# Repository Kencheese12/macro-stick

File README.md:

# macro-stick

縦型Bluetoothマクロパッドの設計データ一式。CKW12ホイールエンコーダ×1＋MXスイッチ×4の1列レイアウト、MCUは Seeed XIAO nRF52840 をエンコーダの下（基板裏面）に配置するB案。全長111.7mm。

## 中身

- `kicad/` — KiCad 10 基板データ
  - `mpad_b.kicad_pcb` — B案の基板（配線済み：Freerouting自動配線＋手修正、DRCクリーン）
  - `mpad_a.kicad_pcb` — A案（参考）
  - `lib/` — 自作フットプリント（mpad.pretty）とSeeed XIAOフットプリント
  - `gen_mpad_b.py` / `gen_mpad.py` — 基板生成スクリプト（KiCad同梱Pythonで実行）
- `case/mpad_case.scad` — 筐体・底板・プレート・スペーサーのOpenSCADデータ（part変数で切替、JLC3DP PA12-S想定）
- `zmk-config/` — ZMK v0.3用ファームウェア設定（このフォルダを独立リポジトリにするとGitHub ActionsでUF2がビルドされる）
- `docs/` — 要件と設計メモ

## キー割り当て

| 位置 | 割り当て |
|---|---|
| KEY1 | Ctrl+C |
| KEY2 | Ctrl+V |
| KEY3 | Ctrl+Z |
| KEY4 | Print Screen |
| エンコーダ回転 | 音量 |
| エンコーダ短押し | ミュート |
| エンコーダ押しながら回転 | スクロール |

設計：GMO天秤AI（基本設計）＋ Muse（KiCad/OpenSCAD検証）

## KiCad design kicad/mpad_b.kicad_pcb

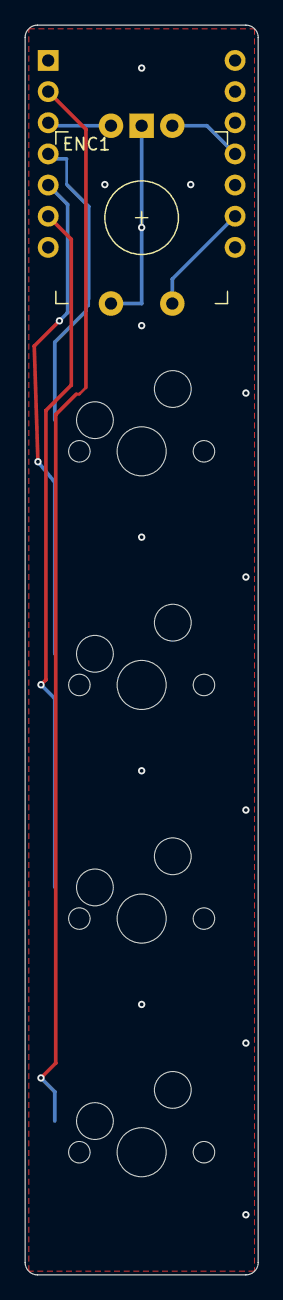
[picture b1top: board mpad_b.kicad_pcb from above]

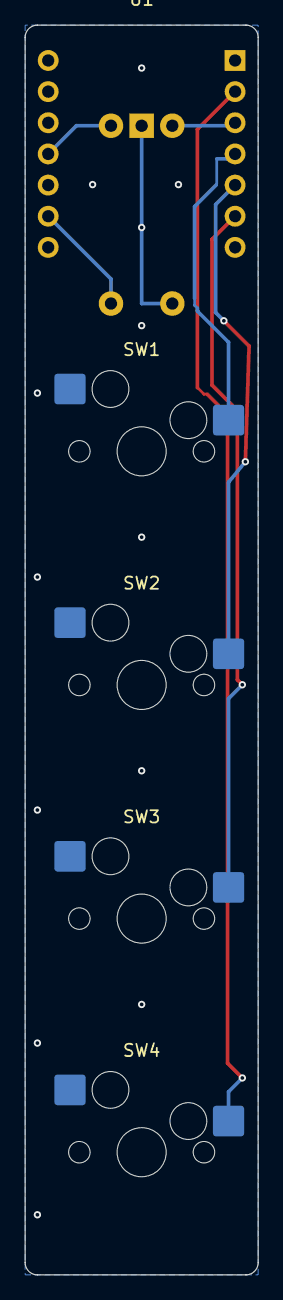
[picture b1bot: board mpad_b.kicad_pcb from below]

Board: 2 copper layers, 19.0 x 101.9 mm, 6 parts (5 on the bottom side), 8 nets.

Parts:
ENC1: CKW12; RotaryEncoder_CKW12_noMP
SW1, SW2, SW3, SW4: CPG151101S11; SW_MX_HS_Kailh_1U_Back
U1: XIAO_nRF52840; XIAO_nRF52840_DIP_Back

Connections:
ENC_A: ENC1.A, U1.11
ENC_B: ENC1.B, U1.3
ENC_SW: ENC1.S1, U1.9
GND: ENC1.C, ENC1.S2, SW1.2, SW2.2, SW3.2, SW4.2, U1.13
KEY1: SW1.1, U1.4
KEY2: SW2.1, U1.5
KEY3: SW3.1, U1.6
KEY4: SW4.1, U1.2

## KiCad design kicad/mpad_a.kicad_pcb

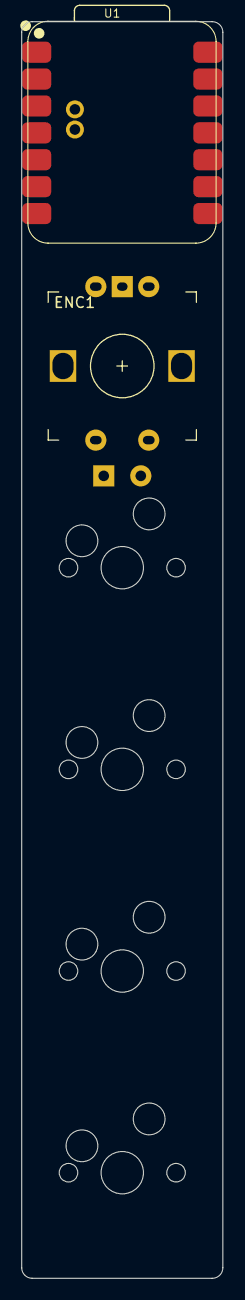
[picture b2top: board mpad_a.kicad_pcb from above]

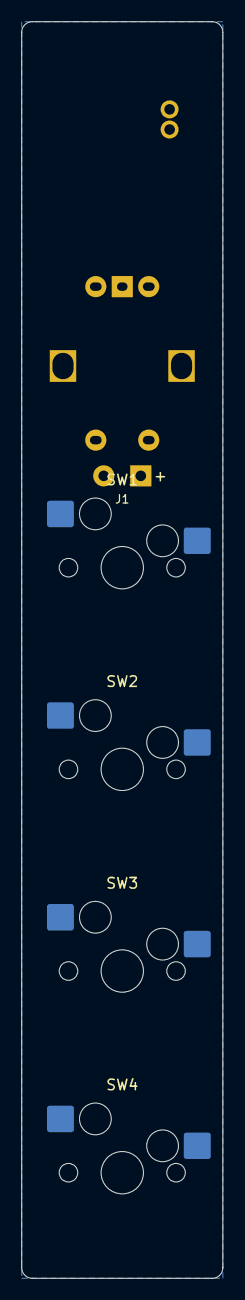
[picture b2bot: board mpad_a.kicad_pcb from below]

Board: 2 copper layers, 19.0 x 118.7 mm, 7 parts (5 on the bottom side), 9 nets, no tracks yet.

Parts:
ENC1: CKW12; RotaryEncoder_EC12_CKW12
J1: LiPo; BattPad_2P_TH_P3.5
SW1, SW2, SW3, SW4: CPG151101S11; SW_MX_HS_Kailh_1U_Back
U1: XIAO_nRF52840; XIAO_nRF52840_SMD_BackAccess

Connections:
BAT+: J1.1, U1.19
ENC_A: ENC1.A, U1.1
ENC_B: ENC1.B, U1.2
ENC_SW: ENC1.S1, U1.3
GND: ENC1.C, ENC1.MP, ENC1.S2, J1.2, SW1.2, SW2.2, SW3.2, SW4.2, U1.13, U1.20
KEY1: SW1.1, U1.4
KEY2: SW2.1, U1.5
KEY3: SW3.1, U1.6
KEY4: SW4.1, U1.9

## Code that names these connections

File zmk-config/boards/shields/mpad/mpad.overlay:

// File: boards/shields/mpad/mpad.overlay
/*
 * 縦長BTマクロパッド（B案）
 * ダイレクト配線: スイッチ → GND、MCU 内蔵プルアップ
 *
 * ENC_SWAP_AB: エンコーダの回転方向が逆なら 1 にする（音量・スクロールが同時に反転）
 * ENC_DETENTS: CKW12 の1回転あたりのクリック数（未確認・暫定 24）
 */
#define ENC_SWAP_AB 0
#define ENC_DETENTS 24

/ {
    chosen {
        zmk,kscan = &kscan0;
    };

    kscan0: kscan {
        compatible = "zmk,kscan-gpio-direct";
        wakeup-source;
        input-gpios
            = <&gpio0 29 (GPIO_ACTIVE_LOW | GPIO_PULL_UP)>   /* pos0 KEY1   D3  P0.29 */
            , <&gpio0 4  (GPIO_ACTIVE_LOW | GPIO_PULL_UP)>   /* pos1 KEY2   D4  P0.04 */
            , <&gpio0 5  (GPIO_ACTIVE_LOW | GPIO_PULL_UP)>   /* pos2 KEY3   D5  P0.05 */
            , <&gpio0 3  (GPIO_ACTIVE_LOW | GPIO_PULL_UP)>   /* pos3 KEY4   D1  P0.03 */
            , <&gpio1 13 (GPIO_ACTIVE_LOW | GPIO_PULL_UP)>   /* pos4 ENC_SW D8  P1.13 */
            ;
    };

    encoder0: encoder {
        compatible = "alps,ec11";
#if ENC_SWAP_AB
        a-gpios = <&gpio0 28 (GPIO_ACTIVE_HIGH | GPIO_PULL_UP)>;   /* ENC_B D2  P0.28 */
        b-gpios = <&gpio1 15 (GPIO_ACTIVE_HIGH | GPIO_PULL_UP)>;   /* ENC_A D10 P1.15 */
#else
        a-gpios = <&gpio1 15 (GPIO_ACTIVE_HIGH | GPIO_PULL_UP)>;   /* ENC_A D10 P1.15 */
        b-gpios = <&gpio0 28 (GPIO_ACTIVE_HIGH | GPIO_PULL_UP)>;   /* ENC_B D2  P0.28 */
#endif
        steps = <(ENC_DETENTS * 4)>;
        status = "okay";
    };

    sensors: sensors {
        compatible = "zmk,keymap-sensors";
        sensors = <&encoder0>;
        triggers-per-rotation = <ENC_DETENTS>;
    };
};
